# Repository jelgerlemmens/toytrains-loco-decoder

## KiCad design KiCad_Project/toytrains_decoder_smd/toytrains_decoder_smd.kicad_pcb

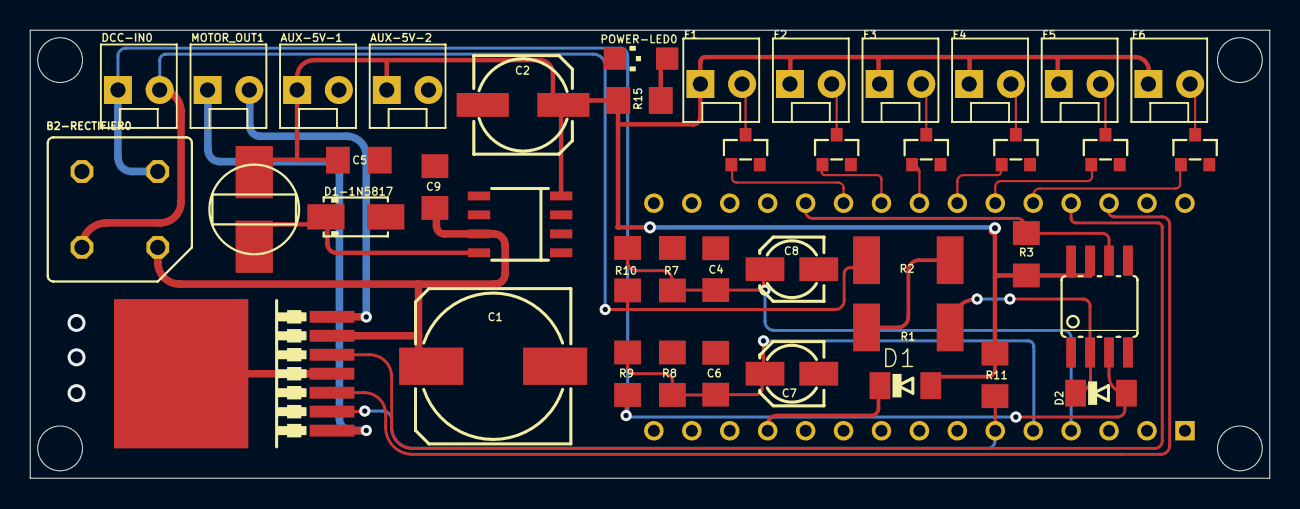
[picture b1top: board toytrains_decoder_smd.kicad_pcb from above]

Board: 2 copper layers, 83.0 x 30.0 mm, 47 parts (1 on the bottom side), 30 nets.

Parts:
ARDUINO_NANO1: ARDUINO_NANO
AUX-5V-1, AUX-5V-2: 5V_OUT; MOLEX-1X2_LOCK_513
B2-RECTIFIER0: 2w10; 1KAB_336
C1: 470uF 35V; 153CLV-1014_334
C2: 100uF 10V; 153CLV-0605_334
C4, C5, C6, C9: 0.1uF; C1206_334
C7, C8: 22uF 16V; 153CLV-0405_334
D1, D2: MINIMELF; MINIMELF_210
D1-1N5817: S1A; DO214AC
DCC-IN0: MOLEX-1X2_LOCK_513
F1, F2, F3, F4, F5, F6: MOLEX-1X2_LOCK_513
IC1: TLE5206-2G; P-TO263-7-1
MOTOR_OUT1: MOLEX-1X2_LOCK_513
OK1: HCPL0601; SOIC08_320
POWER-LED0: CHIPLED_1206_259
Q1, Q2, Q3, Q4, Q5, Q6: BSS138; SOT23
R1, R2: 430Ω; R2512_334
R3: 1kΩ; R1206_334
R7, R8, R11: 2.2kΩ; R1206_334
R9, R10: 10kΩ; R1206_334
R15: 560Ω; R1206_334
U$1: LM2594; SOIC8
U$2: L-CD54; L_CD54
UNK_HOLE_0: dummyfp0
UNK_HOLE_1: dummyfp1
UNK_HOLE_2: dummyfp2
UNK_HOLE_3: dummyfp3

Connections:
5V: AUX-5V-1.1, AUX-5V-2.1, C2.+, C5.1, D1.A, F1.1, F2.1, F3.1, F4.1, F5.1, F6.1, OK1.7, OK1.8, R3.2, R11.1, R15.1, U$1.4, U$2.P$2
20V: B2-RECTIFIER0.+, C1.+, C9.1, IC1.6, U$1.7
GND: ARDUINO_NANO1.14, ARDUINO_NANO1.19, AUX-5V-1.2, AUX-5V-2.2, B2-RECTIFIER0.-, C1.-, C2.-, C4.1, C5.2, C6.2, C7.-, C8.-, C9.2, D1-1N5817.A, IC1.4, IC1.8, OK1.5, POWER-LED0.C, Q1.2, Q2.2, Q3.2, Q4.2, Q5.2, Q6.2, R7.2, R8.2, U$1.5, U$1.6
HV-DCC-SIG-ONE: B2-RECTIFIER0.AC2, D2.A, DCC-IN0.1, OK1.3, R9.1
HV-DCC-SIG-TWO: B2-RECTIFIER0.AC1, DCC-IN0.2, R2.2, R10.1
unnamed: D1-1N5817.C, U$1.8, U$2.P$1
unnamed: ARDUINO_NANO1.22, Q5.1
unnamed: D2.C, OK1.2, R1.1
unnamed: ARDUINO_NANO1.6, IC1.2, R11.2
unnamed: R1.2, R2.1
unnamed: IC1.7, MOTOR_OUT1.2
unnamed: ARDUINO_NANO1.5, C6.1, C7.+, R8.1, R9.2
unnamed: ARDUINO_NANO1.28, IC1.3
unnamed: ARDUINO_NANO1.27, IC1.5
unnamed: ARDUINO_NANO1.21, Q6.1
unnamed: ARDUINO_NANO1.4, C4.2, C8.+, R7.1, R10.2
unnamed: ARDUINO_NANO1.23, Q4.1
unnamed: ARDUINO_NANO1.24, Q3.1
unnamed: ARDUINO_NANO1.25, Q2.1
unnamed: ARDUINO_NANO1.26, Q1.1
unnamed: F6.2, Q1.3
unnamed: F5.2, Q2.3
unnamed: F3.2, Q4.3
unnamed: ARDUINO_NANO1.20, OK1.6, R3.1
unnamed: IC1.1, MOTOR_OUT1.1
unnamed: POWER-LED0.A, R15.2
unnamed: ARDUINO_NANO1.12, D1.C
unnamed: F4.2, Q3.3
unnamed: F2.2, Q5.3
unnamed: F1.2, Q6.3

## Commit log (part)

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2020-10-27 test commit
2020-11-20 H-bridge: TLE5206-G SMD
2020-11-20 H-bridge: TLE5206-G SMD 2
2021-02-11 Included AutoDesk Eagle designs
2026-04-24 esp32_decoder kicad setup
2026-04-24 gitignore updated
2026-04-24 pincontroller updated
